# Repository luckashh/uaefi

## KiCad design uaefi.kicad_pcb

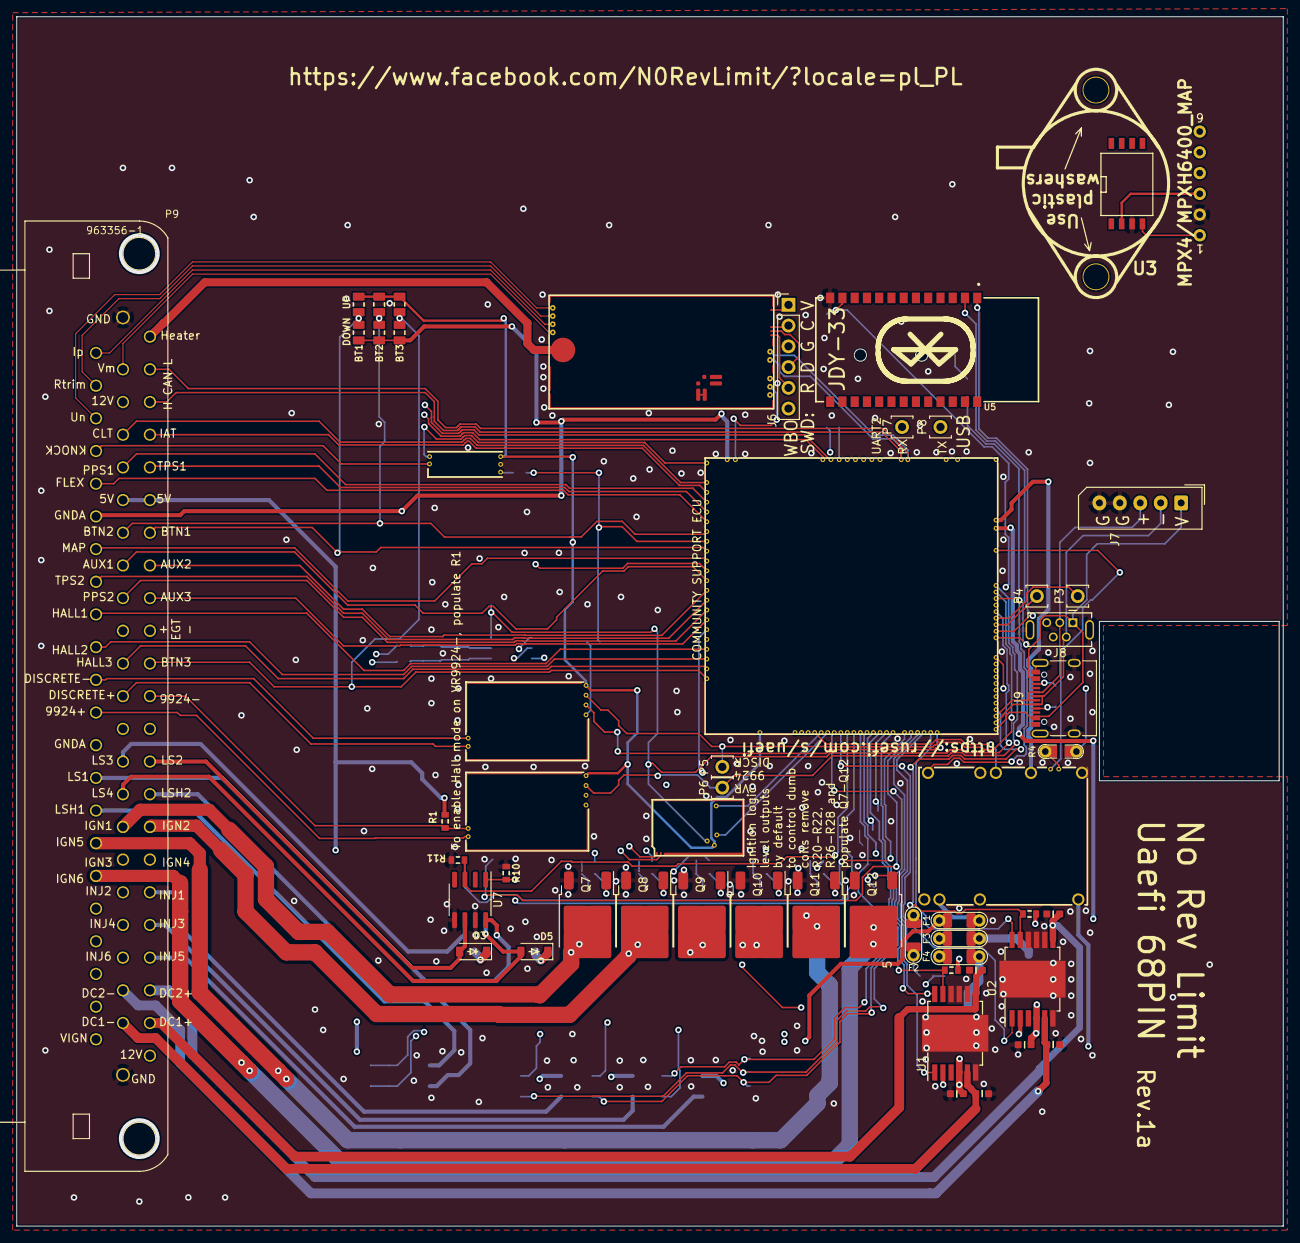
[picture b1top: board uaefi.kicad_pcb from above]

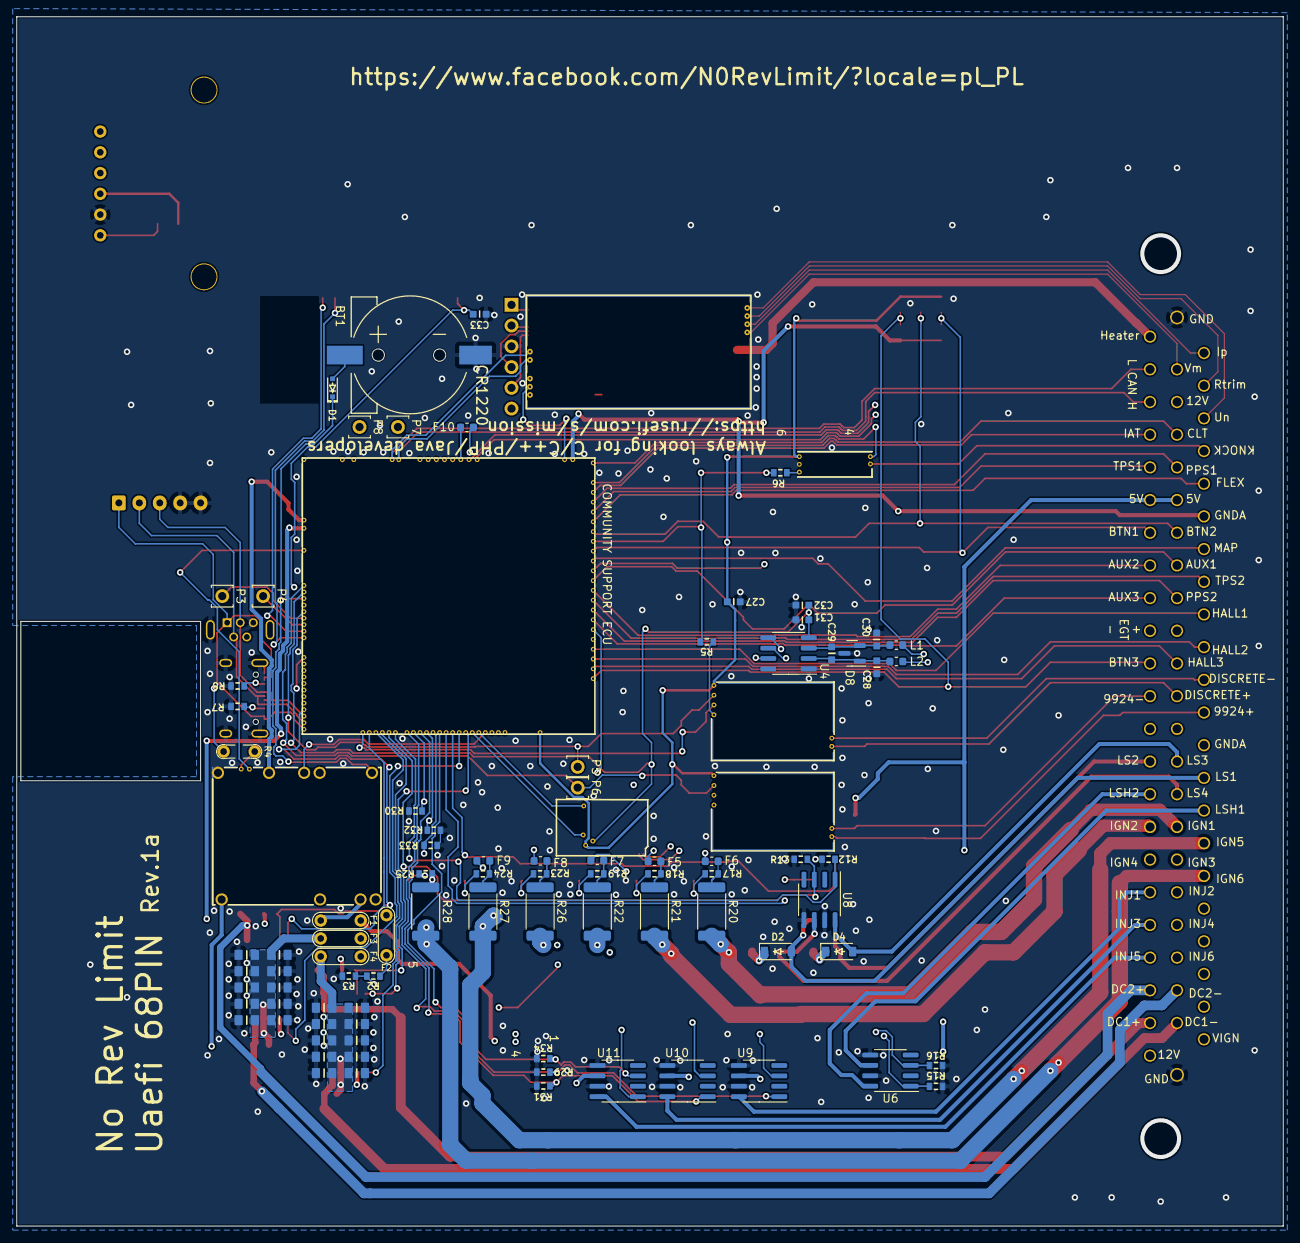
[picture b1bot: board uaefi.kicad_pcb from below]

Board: 4 copper layers, 155.0 x 148.0 mm, 127 parts (74 on the bottom side), 140 nets.

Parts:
BT1: CR1220; CR1220-2
C1, C2, C3, C4, C5, C6, C7, C8, C9, C10, C14, C15, C16, C17, C18, C19, C20, C21, C22, C23: 10u; C0805
C11, C24, C27, C29, C31, C33: 100n; C0603
C12, C13, C25, C26, C28, C30: 10n; C0603
C32: 1u; C0603
D1: 1N4148WS; SOD-323
D2, D3, D4, D5: B5819W; SOD-123
D8: NUP2105L; SOT-23
F1, F2, F3, F4: 12H1500D; PAD-1206-PAD
F5, F6, F7, F8, F9, F10: 50mA; Fuse_0603_1608Metric
J6: Conn_01x06; PinHeader_1x06_P2.54mm_Vertical
J7: Conn_01x05_Male; Molex_SPOX_5267-05A_1x05_P2.50mm_Vertical
J8: USB_B_Mini; USB-MINI-B-VERTICAL
J9: USB_C
L1, L2: 470R@100MHz; L_0603_1608Metric
M1: Module-power_12and5V-0.3; power_12and5V
M2: Module-knock-0.2; knock
M3: Module-vr-discrete-0.5; vr-discrete
M4: Module-vr-max9924-0.1; vr-max9924
M5: Module-wbo-0.5; wbo
M6: Module:mega-mcu100/0.3; mega-mcu100
M7: Module-can-0.1; can
P3, P4, P5, P6, P7, P8: Pad; PAD-TH
P9: 963356-1
Q7, Q8, Q9, Q10, Q11, Q12: ISL9V3040D3ST; TO-252-2
R1, R9, R10, R11, R12, R13, R14, R15, R16, R29, R30, R31, R32, R33, R34: 4.7k; R0603
R2: 33k; R0603
R3: 6.8k; R0603
R4: Jumper-Pad-Pad; PAD-0805-PAD
R5, R6: 0; R0603
R7, R8: 5.6k; R0603
R17, R18, R19, R23, R24, R25: 22; R0603
R20, R21, R22, R26, R27, R28: 0; R_2512_6332Metric
R35, R36, R37: 10k; R0805
R38, R39, R40: DNP; R0805
U1, U2: TLE9201SG; Infineon_PG-DSO-12-11
U3: MPX4/MPXH6400_MAP; MPX-4_MAP
U4: MAX31855KASA; SOIC-8_3.9x4.9mm_P1.27mm
U5: JDY-33
U6, U7, U8, U9, U10, U11: VNLD5160TR-E; SOIC-8_3.9x4.9mm_P1.27mm

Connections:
+3.3V: M6.N21 (V33), R9.2, R14.2, U1.2 (VSO), U2.2 (VSO)
+3.3VA: C31.2, C32.2, C33.2, M6.N15 (V33_SWITCHABLE), M7.V2 (CAN_VIO), U4.4 (V_CC), U5.12 (3V3)
+5V: M1.E4 (V5), M6.N22 (VCC)
+5VA: C27.2, M2.E1 (V5A), M3.E4 (V5_IN), M4.E4 (V5_IN), M5.W1 (V5_IN), M6.E1 (V5A_SWITCHABLE), M6.W2 (V5A_SWITCHABLE), M7.V1 (V5), R38.2, R39.2, R40.2, U3.3 (VCC)
+5VP: M1.V4 (5VP), P9.6, P9.51, R1.1
+12V: F2.1, F3.1, F4.1, P9.68, R2.2
+12V_RAW: D2.1 (K), D3.1 (K), D4.1 (K), D5.1 (K), F2.2, M1.V1 (V12_PERM), M1.V3 (V12_RAW), P9.3
/1_WBO_Ip: M5.E3 (LSU_Ip), P9.24
/2_WBO_Vm: M5.E2 (LSU_Vm), P9.2
/3_WBO_Heater: M5.E5 (LSU_H+), P9.46
/5_WBO_Rtrim: M5.E4 (LSU_Rtrim), P9.25
/6_WBO_Un: M5.E1 (LSU_Un), P9.26
/12V_KEY: F1.1, P9.45
/ADC3: M6.S15 (IN_KNOCK_(PA2)), R5.2, R6.2
/CAN2+: M7.S2 (CANH), P9.58
/CAN2-: M7.S1 (CANL), P9.13
/CAN+: M5.W4 (CANH), M6.W11 (CANH), P9.48
/CAN-: M5.W3 (CANL), M6.W12 (CANL), P9.47
/DC1_DIR: M6.E21 (OUT_PWM4_(PC8)), U1.1 (DIR)
/DC1_DIS: M6.E8 (SPI2_MISO_(PB14)), R9.1, U1.11 (DIS)
/DC1_PWM: M6.E20 (OUT_PWM3_(PC7)), U1.12 (PWM)
/DC2_DIR: M6.E9 (SPI2_MOSI_(PB15)), U2.1 (DIR)
/DC2_DIS: M6.N4 (USBID_(PA10)), R14.1, U2.11 (DIS)
/DC2_PWM: M6.E22 (OUT_PWM5_(PC9)), U2.12 (PWM)
/DC Driver 1/PWR: C1.2, C2.2, C3.2, C4.2, C5.2, C6.2, C7.2, C8.2, C9.2, C10.2, C11.2, F4.2, U1.4 (VS)
/DC Driver 2/PWR: C14.2, C15.2, C16.2, C17.2, C18.2, C19.2, C20.2, C21.2, C22.2, C23.2, C24.2, F3.2, U2.4 (VS)
/EGT+: L1.1, P9.10
/EGT-: L2.1, P9.55
/EGT/SPI_CS: M6.N9 (SPI3_CS_(PA15)), U4.6 (~CS)
/IGN1: F6.2, M6.W10 (IGN1_(PC13))
/IGN2: F5.2, M6.W9 (IGN2_(PE5))
/IGN3: F7.2, M6.W8 (IGN3_(PE4))
/IGN4: F8.2, M6.W7 (IGN4_(PE3))
/IGN5: F9.2, M6.W6 (IGN5_(PE2))
/IGN6: F10.2, M6.W5 (IGN6_(PB8))
/INJ1: M6.E17 (OUT_INJ1_(PD3)), R29.2, U9.1 (IN1)
/INJ2: M6.E16 (OUT_INJ2_(PA9)), R30.2, U9.3 (IN2)
/INJ3: M6.E15 (OUT_INJ3_(PD11)), R31.2, U10.1 (IN1)
/INJ4: M6.E14 (OUT_INJ4_(PD10)), R32.2, U10.3 (IN2)
/INJ5: M6.E13 (OUT_INJ5_(PD2)), R33.2, U11.1 (IN1)
/INJ6: M6.E12 (OUT_INJ6_(PA8)), R34.2, U11.3 (IN2)
/INTERNAL_MAP: M6.S12 (IN_MAP2_(PC1)), U3.1 (VOUT)
/IN_AUX1: M6.S11 (IN_O2S_/_CAN_WAKEUP_(PA0)), P9.8
/IN_AUX2: M6.S10 (IN_O2S2_(PA1)), P9.53
/IN_AUX3: M6.S7 (IN_AUX3_(PA7)), P9.54
/IN_BUTTON1: M6.S14 (IN_CRANK_(PB1)), P9.52, R35.2, R38.1
/IN_BUTTON2: M6.S16 (IN_CAM_(PA6)), P9.7, R36.2, R39.1
/IN_BUTTON3: M6.S1 (IN_D4_(PE15)), P9.56, R37.2, R40.1
/IN_CLT: M6.S21 (IN_CLT_(PC2)), P9.4
/IN_FLEX: M6.S17 (IN_VSS_(PE11)), P9.28
/IN_HALL1: M6.S4 (IN_D1_(PE12)), P9.32
/IN_HALL2: M6.S3 (IN_D2_(PE13)), P9.33
/IN_HALL3: M6.S2 (IN_D3_(PE14)), P9.11
/IN_IAT: M6.S20 (IN_IAT_(PC3)), P9.49
/IN_KNOCK: M2.E3 (OUT_KNOCK), R6.1
/IN_KNOCK_RAW: M2.W1 (IN_KNOCK), P9.27
/IN_MAP: M6.S13 (IN_MAP1_(PC0)), P9.30
/IN_PPS1: M6.S19 (IN_PPS_(PA3)), P9.5
/IN_PPS2: M6.S8 (IN_AUX2_(PC4/PE9)), P9.9
/IN_TPS1: M6.S18 (IN_TPS_(PA4)), P9.50
/IN_TPS2: M6.S9 (IN_AUX1_(PB0)), P9.31
/IN_VIGN: F1.2, M1.V2 (IN_VIGN)
/IN_VMAIN: M6.S6 (IN_AUX4_(PC5)), R2.1, R3.2
/LS1: M6.E11 (OUT_INJ7_(PD15)), R10.2, U7.1 (IN1)
/LS2: M6.E10 (OUT_INJ8_(PD12)), R11.2, U7.3 (IN2)
/LS3: M6.E18 (OUT_PWM1_(PD13)), R12.2, U8.1 (IN1)
/LS4: M6.E19 (OUT_PWM2_(PC6)), R13.2, U8.3 (IN2)
/LS_HOT1: M6.W4 (IGN7_(PB9)), R16.1, U6.3 (IN2)
/LS_HOT2: M6.W3 (IGN8_(PE6)), R15.1, U6.1 (IN1)
/MISO3: M6.N11 (SPI3_MISO_(PC11)), U4.7 (SO)
/OUT_DC1+: C13.2, P9.67, U1.7 (OUT2)
/OUT_DC1-: C12.2, P9.22, U1.5 (OUT1)
/OUT_DC2+: C26.2, P9.66, U2.7 (OUT2)
/OUT_DC2-: C25.2, P9.21, U2.5 (OUT1)
/OUT_IGN1: P9.16, Q7.2 (C), R20.2
/OUT_IGN2: P9.61, Q8.2 (C), R21.2
/OUT_IGN3: P9.17, Q9.2 (C), R22.2
/OUT_IGN4: P9.62, Q10.2 (C), R26.2
/OUT_IGN5: P9.39, Q11.2 (C), R27.2
/OUT_IGN6: P9.40, Q12.2 (C), R28.2
/OUT_INJ1: P9.63, U9.8 (D1)
/OUT_INJ2: P9.18, U9.6 (D2)
/OUT_INJ3: P9.64, U10.8 (D1)
/OUT_INJ4: P9.19, U10.6 (D2)
/OUT_INJ5: P9.65, U11.8 (D1)
/OUT_INJ6: P9.20, U11.6 (D2)
/OUT_LS1: D2.2 (A), P9.37, U7.8 (D1)
/OUT_LS2: D3.2 (A), P9.59, U7.6 (D2)
/OUT_LS3: D4.2 (A), P9.14, U8.8 (D1)
/OUT_LS4: D5.2 (A), P9.15, U8.6 (D2)
/OUT_LS_HOT1: P9.38, U6.6 (D2)
/OUT_LS_HOT2: P9.60, U6.8 (D1)
/PG_5VP: M6.N12 (SPI3_MOSI_(PC12)), R4.2
/PWR_EN: M1.E5 (EN_5VP), M6.N20 (OUT_PWR_EN_(PE10))
/SCK3: M6.N10 (SPI3_SCK_(PC10)), U4.5 (SCK)
/USB+: J7.3, J8.3 (D+), J9.A6 (D+), J9.B6 (D+), M6.N3 (USBP_(PA12))
/USB-: J7.2, J8.2 (D-), J9.A7 (D-), J9.B7 (D-), M6.N2 (USBM_(PA11))
/VBAT: D1.1 (K), M1.E1 (VBAT), M6.N17 (VBAT)
/VBUS: J7.1, J8.1 (VBUS), J9.A4 (VBUS), J9.A9 (VBUS), J9.B4 (VBUS), J9.B9 (VBUS), M6.N1 (VBUS)
/VIGN: M1.E3 (VIGN), M6.E5 (IN_VIGN_(PA5))
/VREF1: M2.W2 (VREF), M6.S22 (VREF1)
/VR_DISCRETE: M3.E3 (OUT), M6.N18 (UART8_RX_(PE0)), P5.1
/VR_DISCRETE+: M3.W2 (VR+), P9.12
/VR_DISCRETE-: M3.W1 (VR-), P9.34
/VR_DISCRETE_A: M3.E2 (OUT_A), R5.1
/VR_DISCRETE_THR: M3.E1 (Thresh_IN), M6.E23 (OUT_PWM6_(PD14))
/VR_MAX9924: M4.E3 (OUT), M6.N19 (UART8_TX_(PE1)), P6.1
/VR_MAX9924+: M4.W2 (VR+), P9.35
/VR_MAX9924-: M4.W1 (VR-), P9.57, R1.2
GND: BT1.2 (-), C1.1, C2.1, C3.1, C4.1, C5.1, C6.1, C7.1, C8.1, C9.1, C10.1, C11.1, C12.1, C13.1, C14.1, C15.1, C16.1, C17.1, C18.1, C19.1, C20.1, C21.1, C22.1, C23.1, C24.1, C25.1, C26.1, C27.1, C28.1, C30.1, C31.1, C32.1, C33.1, D8.3 (A), J6.3, J7.4, J7.5, J8.5 (GND), J8.6 (Shield), J9.A1 (GND), J9.A12 (GND), J9.B1 (GND), J9.B12 (GND), J9.S1 (SHIELD), M1.S1 (GND), M2.E2 (GND), M3.G (GND), M4.G (GND), M5.E6 (LSU_H-), M5.G (GND), M6.G (GND), M7.E1 (GND), P9.1, P9.23, Q7.3 (E), Q8.3 (E), Q9.3 (E), Q10.3 (E), Q11.3 (E), Q12.3 (E), R3.1, R7.1, R8.1, R10.1, R11.1, R12.1, R13.1, R15.2, R16.2, R29.1, R30.1, R31.1, R32.1, R33.1, R34.1, U1.6 (GND), U1.8 (SI), U1.9 (CSN), U1.10 (SCK), U1.13 (GND), U2.6 (GND), U2.8 (SI), U2.9 (CSN), U2.10 (SCK), U2.13 (GND), U3.2 (GND), U4.1 (GND), U5.13 (GND), U6.5 (S2), U6.7 (S1), U7.5 (S2), U7.7 (S1), U8.5 (S2), U8.7 (S1), U9.5 (S2), U9.7 (S1), U10.5 (S2), U10.7 (S1), U11.5 (S2), U11.7 (S1)
GNDA: M6.W1 (GNDA), P9.29, P9.36, R35.1, R36.1, R37.1
unnamed: BT1.1 (+), D1.2 (A)
unnamed: F5.1, R18.2, R21.1
unnamed: F6.1, R17.2, R20.1
unnamed: F7.1, R19.2, R22.1
unnamed: F8.1, R23.2, R26.1
unnamed: F9.1, R24.2, R27.1
unnamed: F10.1, R25.2, R28.1
unnamed: J6.1, M5.W8 (V33_OUT)
unnamed: J6.2, M5.W7 (SWCLK)
unnamed: J6.4, M5.W6 (SWDIO)
unnamed: J6.5, M5.W5 (nReset)
unnamed: J9.A5 (CC1), R7.2
unnamed: J9.B5 (CC2), R8.2
unnamed: M1.E6 (PG_5VP), R4.1
unnamed: M5.J1 (SEL1), M5.J_GND1 (PULL_DOWN1)
unnamed: M6.N14a (LED_GREEN), P4.1
unnamed: M6.N14b (LED_YELLOW), P3.1
unnamed: M6.E6 (SPI2_CS_/_CAN2_RX_(PB12)), M7.V6 (CAN_RX)
unnamed: M6.E7 (SPI2_SCK_/_CAN2_TX_(PB13)), M7.V5 (CAN_TX)
unnamed: M6.N14 (UART2_RX_(PD6)), P7.1, U5.1 (TXD)
unnamed: M6.N13 (UART2_TX_(PD5)), P8.1, U5.2 (RXD)
unnamed: Q7.1 (G), R17.1
unnamed: Q8.1 (G), R18.1
unnamed: Q9.1 (G), R19.1
unnamed: Q10.1 (G), R23.1
unnamed: Q11.1 (G), R24.1
unnamed: Q12.1 (G), R25.1
unnamed: C29.2, C30.2, D8.2 (K), L1.2, U4.3 (T+)
unnamed: C28.2, C29.1, D8.1 (K), L2.2, U4.2 (T-)

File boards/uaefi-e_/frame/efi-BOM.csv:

Comment,Designator,Footprint,LCSC Part #
"CR1220","BT1","CR1220-2","C70381"
"10u","C1","C0805","C15850"
"10u","C2","C0805","C15850"
"10u","C3","C0805","C15850"
"10u","C4","C0805","C15850"
"10u","C5","C0805","C15850"
"10u","C6","C0805","C15850"
"10u","C7","C0805","C15850"
"10u","C8","C0805","C15850"
"10u","C9","C0805","C15850"
"10u","C10","C0805","C15850"
"100n","C11","C0603","C14663"
"10n","C12","C0603","C57112"
"10n","C13","C0603","C57112"
"10u","C14","C0805","C15850"
"10u","C15","C0805","C15850"
"10u","C16","C0805","C15850"
"10u","C17","C0805","C15850"
"10u","C18","C0805","C15850"
"10u","C19","C0805","C15850"
"10u","C20","C0805","C15850"
"10u","C21","C0805","C15850"
"10u","C22","C0805","C15850"
"10u","C23","C0805","C15850"
"100n","C24","C0603","C14663"
"10n","C25","C0603","C57112"
"10n","C26","C0603","C57112"
"100n","C27","C0603","C14663"
"10n","C28","C0603","C57112"
"100n","C29","C0603","C14663"
"10n","C30","C0603","C57112"
"100n","C31","C0603","C14663"
"1u","C32","C0603","C15849"
"100n","C33","C0603","C14663"
"1N4148WS","D1","SOD-323","C2128"
"B5819W","D2","SOD-123","C8598"
"B5819W","D3","SOD-123","C8598"
"B5819W","D4","SOD-123","C8598"
"B5819W","D5","SOD-123","C8598"
"NUP2105L","D8","SOT-23","C284104"
"12H1500D","F1","PAD-1206-PAD","C182446"
"12H1500D","F2","PAD-1206-PAD","C182446"
"12H1500D","F3","PAD-1206-PAD","C182446"
"12H1500D","F4","PAD-1206-PAD","C182446"
"50mA","F5","Fuse_0603_1608Metric","C369141"
"50mA","F6","Fuse_0603_1608Metric","C369141"
"50mA","F7","Fuse_0603_1608Metric","C369141"
"50mA","F8","Fuse_0603_1608Metric","C369141"
"50mA","F9","Fuse_0603_1608Metric","C369141"
"50mA","F10","Fuse_0603_1608Metric","C369141"
"Conn_01x06","J6","PinHeader_1x06_P2.54mm_Vertical","C37208"
"Conn_01x05_Male","J7","Molex_SPOX_5267-05A_1x05_P2.50mm_Vertical",""
"USB_B_Mini","J8","USB-MINI-B-VERTICAL",""
"USB_C","J9","USB_C","C2927038"
"470R@100MHz","L1","L_0603_1608Metric","C97853"
"470R@100MHz","L2","L_0603_1608Metric","C97853"
"Module:power_12and5V/0.3","M1","power_12and5V",""
"Module:knock/0.2","M2","knock",""
"Module:vr-discrete/0.5","M3","vr-discrete",""
"Module:vr-max9924/0.1","M4","vr-max9924",""
"Module:wbo/0.5","M5","wbo",""
"Module:mega-mcu100/0.3","M6","mega-mcu100",""
"Module:can/0.1","M7","can",""
"Pad","P3","PAD-TH",""
"Pad","P4","PAD-TH",""
"Pad","P5","PAD-TH",""
"Pad","P6","PAD-TH",""
"Pad","P7","PAD-TH",""
"Pad","P8","PAD-TH",""
"963356-1","P9","963356-1",""
"ISL9V3040D3ST","Q7","DPAK",""
"ISL9V3040D3ST","Q8","DPAK",""
"ISL9V3040D3ST","Q9","DPAK",""
"ISL9V3040D3ST","Q10","DPAK",""
"ISL9V3040D3ST","Q11","DPAK",""
"ISL9V3040D3ST","Q12","DPAK",""
"4.7k","R1","R0603",""
"33k","R2","R0603","C4216"
"6.8k","R3","R0603","C23212"
"Jumper-Pad-Pad","R4","PAD-0805-PAD","C17477"
"0","R5","R0603",""
"0","R6","R0603","C21189"
"5.6k","R7","R0603","C23189"
"5.6k","R8","R0603","C23189"
"4.7k","R9","R0603","C23162"
"4.7k","R10","R0603","C23162"
"4.7k","R11","R0603","C23162"
"4.7k","R12","R0603","C23162"
"4.7k","R13","R0603","C23162"
"4.7k","R14","R0603","C23162"
"4.7k","R15","R0603","C23162"
"4.7k","R16","R0603","C23162"
"22","R17","R0603","C23345"
"22","R18","R0603","C23345"
"22","R19","R0603","C23345"
"0","R20","R2512","C25469"
"0","R21","R2512","C25469"
"0","R22","R2512","C25469"
"22","R23","R0603","C23345"
"22","R24","R0603","C23345"
"22","R25","R0603","C23345"
"0","R26","R2512","C25469"
"0","R27","R2512","C25469"
"0","R28","R2512","C25469"
"4.7k","R29","R0603","C23162"
"4.7k","R30","R0603","C23162"
"4.7k","R31","R0603","C23162"
"4.7k","R32","R0603","C23162"
"4.7k","R33","R0603","C23162"
"4.7k","R34","R0603","C23162"
"10k","R35","R0805","C17414"
"10k","R36","R0805","C17414"
"10k","R37","R0805","C17414"
"DNP","R38","R0805",""
"DNP","R39","R0805",""
"DNP","R40","R0805",""
"TLE9201SG","U1","Infineon_PG-DSO-12-11","C112633"
"TLE9201SG","U2","Infineon_PG-DSO-12-11","C112633"
"MPX4/MPXH6400_MAP","U3","MPX-4_MAP",""
"MAX31855KASA","U4","SO8","C52028"
"JDY-33","U5","JDY-33","C9900001612"
"VNLD5160TR-E","U6","SO8","C377942"
"VNLD5160TR-E","U7","SO8","C377942"
"VNLD5160TR-E","U8","SO8","C377942"
"VNLD5160TR-E","U9","SO8","C377942"
"VNLD5160TR-E","U10","SO8","C377942"
"VNLD5160TR-E","U11","SO8","C377942"

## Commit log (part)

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2025-12-27 zmiana 1
2025-12-27 zmiana1b
2025-12-27 zmiana3
2025-12-27 Zmiana 6.8k
2025-12-27 zmiana 10k
2025-12-27 [skip actions] Auto-generated board v2.1
2026-01-02 uaefi 68pin
2026-01-04 can2, egt, przesyniecie pcb
